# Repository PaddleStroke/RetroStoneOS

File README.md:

# RetroStoneOS

**A fast, minimal retro-gaming OS for the RetroStone2 handheld, and for Raspberry Pi and Orange Pi boards.**

RetroStoneOS boots straight into an EmulationStation-style menu **in about two seconds**, plays games from 40
systems, and switches between the built-in screen and a TV **live, just by plugging HDMI in**. It replaces the old
RetrOrangePi stack (Armbian + RetroPie + RetroArch + EmulationStation) with one small, purpose-built system: mainline
Linux, a single menu/emulation program written in C, and libretro emulator cores. There's no desktop, no X11 and no
layer cake, and every setting lives in one menu.

## Features

**Fast**
- About 2 s from power-on to the logo, and the menu about 0.3 s later. The menu is drawn from a snapshot while game lists load in the background.
- Theme art is prefetched in the background, so a system's first visit in the carousel does not stutter.
- Shutdown in about a second. Powering off during a game saves it; at the next boot the game resumes **Always**, **Ask** or **Never** (your choice).

**Plays well**
- Hardware-scaled video (pixel-perfect 2x on the RetroStone2 LCD) with audio/video sync and dynamic rate control.
- 60 Hz LCD mode, per-game core options, **per-game scaling and CPU profile**, save states with thumbnails, auto-save on exit.
- Each game runs in its own process: a crashing emulator can't take the menu down.
- N64 with GPU rendering and a shader cache, plus an in-game **benchmark** that finds the fastest settings for each game.
- **Rumble** on pads that have motors.

**Laptop-style display switching**
- Plug HDMI in and the picture moves to the TV (720p, or 640x480 for the retro look). Unplug it and it's back on the LCD, even mid-game.
- In docked mode, the controller that starts a game becomes player 1.

**Controls**
- Built-in buttons and the analog stick are handled by the kernel. USB/Bluetooth pads are recognised automatically (SDL GameControllerDB).
- RetroPie hotkeys: **Select+Start** exit, **Select+R/L** save/load state, **Select+Left/Right** state slot, **Select+X** in-game menu, **Select+B** reset.
- **Select+R2** fast-forward, **Select+L2** screenshot, **Select+Y** game switcher (jump between your recent games, each resumed where you left it).
- Remaps per system and per game, including the RetroStone2's optional 6-button Mega Drive layout.

**Finding games**
- **Letter jump** and **search** (in one list or across all games).
- **Play time** per game and a **"Most played"** list, next to favourites and recently played.
- **Hide** or **delete** a game from the menu.

**Getting games on it**
- **SD card in a PC:** the `RETROSTONE` drive, ready right after flashing.
- **USB stick:** plug it in, then *Import games*, *Export games* or *Back up saves*. Copies are incremental, with duplicate handling.
- **WiFi/Ethernet:** a drag-and-drop web page (PIN-protected, with a QR code), or the **Windows share** `\\RETROSTONE`.

**Updates**
- **Signed over-the-air updates** from Settings > System update (WiFi), or offline from a USB drive or the SD card.
- The new system goes to the other A/B slot and is checked before the switch; if it doesn't start, the console goes back to the previous one by itself. Games, saves and settings are never touched. See [docs/updates.md](docs/updates.md).

**Handheld care**
- Battery gauge and warnings, a clean save and shutdown at critical battery, a charge-only mode, and idle dimming.
- **Idle power-off**: after 5 minutes without input (Settings > Power > "Power off after", or Never) the console saves the game and powers off, after a 10 s notice that any button cancels.
- Panel care on the RetroStone2: the LCD keeps receiving a picture whenever it is powered (its "screen off" is backlight off plus a black frame), which protects the panel.
- The SD card is checked after an unexpected power loss, and a hardware watchdog guards against hangs.
- The first boot can't hang on its "Preparing the SD card" screen, and it leaves a step-by-step trace (`rsos/logs/firstboot.txt` on the card) for bug reports.
- WiFi, Bluetooth and Ethernet are **off by default**, so they cost no boot time or battery.

**Looks**
- EmulationStation theme support (drop any ES theme in `themes/`).
- Built-in **rsos-dark** and **rsos-light** themes with console art, plus the **gbz35** themes.
- **22 languages**, chosen at the first boot (English, French, German, Spanish, Italian, Portuguese, Japanese, Chinese, Korean, Russian and more).

## Systems

| Family | Systems |
|---|---|
| RetroStone | 8BCraft's own games, built in: Bomber Mole, Leady Squid, Duck Parade, Blueberry Tumble, Beaver Rush, Pancake Tower and Pogo Mamie (RetroStone VC, [docs/vc-games.md](docs/vc-games.md)) |
| Nintendo | NES, Famicom Disk System, SNES, Nintendo 64, Game Boy, Game Boy Color, Game Boy Advance, Pokémon mini |
| Sega | Master System, Mega Drive/Genesis, Game Gear, SG-1000, 32X, Mega-CD, Pico |
| Sony | PlayStation |
| NEC | PC Engine/TurboGrafx-16, PC Engine CD, SuperGrafx |
| SNK | Neo Geo, Neo Geo CD, Neo Geo Pocket (Color) |
| Arcade | MAME 2003-Plus, FinalBurn Neo |
| Computers | MS-DOS (DOSBox Pure), Commodore 64, ZX Spectrum, Amstrad CPC, MSX |
| Game engines and ports | ScummVM, Doom (Freedoom included), Cave Story, PICO-8 (fake-08) |
| Others | Atari 2600/7800/Lynx, WonderSwan (Color), ColecoVision |

Pre-installed games, so the console is fun out of the box: the **RetroStone** system (Bomber Mole, Leady Squid, Duck Parade, Blueberry Tumble, Beaver Rush, Pancake Tower and Pogo Mamie),
**µCity** (Game Boy Color, GPL-3.0+ / CC BY-SA 4.0) and **Freedoom** (Doom, BSD-3-Clause); see
[docs/homebrew.md](docs/homebrew.md) and [docs/vc-games.md](docs/vc-games.md).
BIOS files go in `RETROSTONE/bios/` (see [docs/cores.md](docs/cores.md)). No commercial games or BIOS files are included.

## Supported hardware

| Board | Defconfig | Status |
|---|---|---|
| **RetroStone2** (8BCraft, Allwinner A20) | `retrostone2` | Primary target, tested |
| RetroStone1 (8BCraft, Allwinner H3) | `retrostone1` | Untested, built by CI; built-in screen (composite) compile-tested only |
| Raspberry Pi 2 (and Pi 3 / Zero 2 W in 32-bit mode) | `rpi2` | Untested, built by CI |
| Raspberry Pi 3 / Zero 2 W (64-bit) | `rpi3_64` | Untested, built by CI |
| Raspberry Pi 4 / 400 / CM4 | `rpi4_64` | Untested, built by CI |
| Raspberry Pi 5 / 500 | `rpi5_64` | Untested, built by CI |
| Orange Pi PC / PC Plus (H3) | `orangepi_h3_pc` | Untested, built by CI |
| Orange Pi One / Lite (H3) | `orangepi_h3_one` | Untested, built by CI |
| Orange Pi 5 (RK3588S) | `orangepi5` | Untested, built by CI |

The single-board computer images are built automatically by CI, but nobody has booted them on the board yet: they
are HDMI boxes for USB/Bluetooth pads. Please open an issue with your results! Details in [docs/boards.md](docs/boards.md);
adding a board takes one folder and a `board.ini` profile ([docs/porting.md](docs/porting.md)).

## Install

1. Download the image for your board from [**Releases**](https://github.com/PaddleStroke/RetroStoneOS/releases).
2. Flash it to a microSD card of 2 GB or more (4 GB for the Orange Pi 5) with [balenaEtcher](https://etcher.balena.io/) or [Rufus](https://rufus.ie/).
3. Copy your games into `RETROSTONE/roms/<system>/`, from the PC (the drive appears right after flashing), from a USB stick, or over WiFi later.
4. Boot. The first start prepares the SD card and asks for your language, then the menu appears.

Later versions install from the console itself (Settings > System update); no reflashing needed.

## Build from source

RetroStoneOS is a [Buildroot](https://buildroot.org/) external tree. On Linux (or WSL2):

```sh
wget https://buildroot.org/downloads/buildroot-2026.02.3.tar.xz && tar xf buildroot-2026.02.3.tar.xz
cd buildroot-2026.02.3
make BR2_EXTERNAL=/path/to/RetroStoneOS/buildroot-external retrostone2_defconfig   # or rpi4_64_defconfig, ...
make
# -> output/images/sdcard.img
```

The RetroStone games build from a [RetroStone VC](https://github.com/PaddleStroke/RetroStoneVC) checkout next to
this one (`../RetroStoneVC`; or set `BR2_PACKAGE_RSOS_VC_GAMES=n`, docs/vc-games.md). The menu
program also builds and tests on a PC: `cd frontend && make check`. Details: [docs/build.md](docs/build.md).

## Documentation

| | |
|---|---|
| [build.md](docs/build.md) | Building, the SD layout, A/B slots, boot time, the release build |
| [boards.md](docs/boards.md) · [porting.md](docs/porting.md) | Supported boards; adding a board |
| [cores.md](docs/cores.md) | Emulators, BIOS files, ROM folders, performance |
| [ui-design.md](docs/ui-design.md) | The menu, themes, settings |
| [host-design.md](docs/host-design.md) | The libretro game host (hotkeys, fast-forward, screenshots, game switcher) |
| [input-design.md](docs/input-design.md) | Controls, remaps, rumble |
| [display-design.md](docs/display-design.md) | LCD/HDMI switching and scaling |
| [rom-transfer.md](docs/rom-transfer.md) | USB, web page and Windows share |
| [updates.md](docs/updates.md) | Signed system updates (`.rsu` packages, keys) |
| [power.md](docs/power.md) | Battery, charging, shutdown |
| [translating.md](docs/translating.md) | Adding or fixing a translation |
| [homebrew.md](docs/homebrew.md) | The bundled games and their licences |
| [vc-games.md](docs/vc-games.md) | The RetroStone system: 8BCraft's own games (RetroStone VC) |
| [ci.md](docs/ci.md) | CI, releases and the repository secrets |
| [hardware-pinmap.md](docs/hardware-pinmap.md) · [kernel-patches.md](docs/kernel-patches.md) | RetroStone2 hardware and kernel patches |
| [bringup.md](docs/bringup.md) | Hardware test script ([bring-up logs](docs/bringup-logs/)) |
| [hardware/](hardware/) | RetroStone2 schematic, PCB and Gerber files; RetroStone1 schematic and PCB |
| [CONVENTIONS.md](docs/CONVENTIONS.md) · [requirements.md](docs/requirements.md) · [review/](docs/review/) | Project conventions, requirements and reviews |

## License

The RetroStoneOS code is under the [MIT License](LICENSE). Bundled third-party components keep their own licences (the
Linux kernel and U-Boot under GPL-2.0, the emulator cores under various licences including some non-commercial ones,
the Carbon/gbz35 theme art under CC BY-NC-SA, and the RetroStone games under MIT (code) and CC BY-NC-SA 4.0 (art,
music, levels)). See [LICENSE](LICENSE) for the details, and each release's
`legal-info` archive for the full sources and licence texts. The hardware files in `hardware/` (RetroStone2 and
RetroStone1) are open hardware under the [CERN-OHL-P-2.0](hardware/LICENSE.txt) (see [hardware/README.md](hardware/README.md)).

**The images are free, for non-commercial use.** RetroStoneOS is a free download and is not sold with any hardware.
Its images include non-commercial emulator cores (snes9x2005/2010, PicoDrive, MAME 2003-Plus, FBNeo) and CC BY-NC-SA
theme art, so an image must not be sold, and must not be preloaded on hardware that is sold (a console, an SD card
or a kit). Sharing the images for free is fine.

## Credits

- The RetroStone2 handheld: **Pierre-Louis Boyer / 8BCraft**.
- The [libretro](https://www.libretro.com/) core authors, [Buildroot](https://buildroot.org/), the
  [linux-sunxi](https://linux-sunxi.org/) community and the mainline kernel developers.
- Olimex, for the original A20 HDMI audio driver work.
- Themes: rxbrad (gbz35) and Rookervik (Carbon, RetroPie).
- Antonio Niño Díaz for µCity, and the Freedoom project (see [docs/homebrew.md](docs/homebrew.md)).

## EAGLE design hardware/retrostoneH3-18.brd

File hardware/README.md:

# RetroStone hardware files

Design files of the RetroStone2 main board (Allwinner A20) and of the RetroStone1 (Allwinner H3), by Pierre-Louis
Boyer / 8BCraft. The RetroStone2 files are the source of
truth for the pin map in [docs/hardware-pinmap.md](../docs/hardware-pinmap.md) and for the device tree
(`buildroot-external/board/retrostone2/dts/`). The folder also holds the RetroStone1 (Allwinner H3) schematic and
layout, the source of `buildroot-external/board/retrostone1/dts/`.

| File | Content |
|---|---|
| `retrostoneA20-1.15.sch` | schematic, board revision 1.15 (Eagle 7.6, XML) |
| `retrostoneA20-1.15.brd` | PCB layout, revision 1.15 (Eagle 7.6, XML) |
| `retrostoneA20-1.15.pdf` | the schematic as a PDF |
| `retrostone2_v1.15.zip` | Gerber and drill files, revision 1.15 |
| `retrostoneA20-1.08.xls` | bill of materials, revision 1.08 (older board) |
| `retrostoneH3-18.sch` | **RetroStone1** (Allwinner H3) schematic, revision 1.18 (Eagle 7.6, XML); source of `buildroot-external/board/retrostone1/dts/` (docs/boards.md, "RetroStone1") |
| `retrostoneH3-18.brd` | RetroStone1 PCB layout, revision 1.18 (Eagle 7.6, XML) |
| `RSN1-1.18.pdf` | the RetroStone1 schematic as a PDF (vector drawing, no text layer) |
| `tools/eagle_nets.py` | lists the parts and nets of a `.sch`: `python3 tools/eagle_nets.py <sch> parts\|part <name>\|net <name>` |
| `tools/eagle_parts_pos.py` | prints the board position of parts from a `.brd`: `python3 tools/eagle_parts_pos.py <brd> K1 K2 ...` |

## Known design notes (for future revisions)

- **RetroStone1: MCP3208 CH2 wired straight to VBAT.** The battery voltage goes to the ADC input without a divider:
  a charged cell (4.2 V) is above the MCP3208's absolute maximum input (VDD + 0.6 V at 3.3 V), and while the 3.3 V
  rail is off the input's protection diode back-feeds that rail from the battery. The owner does not plan to
  produce this board again; a new revision should use a divider (e.g. 2 x 100k, with a small capacitor) or a
  dedicated gauge.
- **RetroStone2: the panel VCC is the always-on 3.3 V rail**, and that rail (buck U17) is enabled by the AXP209
  EXTEN output together with the 5 V boost and the speaker amplifier: a load switch on the panel VCC driven by a
  free GPIO is worth adding (docs/hardware-pinmap.md, "Panel power" and "Power").

## Licence

The design files in this folder (not `tools/`) are open hardware, © 2026 Pierre-Louis Boyer / 8BCraft, licensed
under the **CERN Open Hardware Licence Version 2 – Permissive** (SPDX: `CERN-OHL-P-2.0`, full text in
[LICENSE.txt](LICENSE.txt)). You may study, modify, make and sell boards from them; keep the copyright and licence
notices. The scripts in `tools/` are under the MIT licence of the RetroStoneOS software ([LICENSE](../LICENSE)).
"RetroStone" and "8BCraft" are names of 8BCraft: a derived board should not be sold under them.

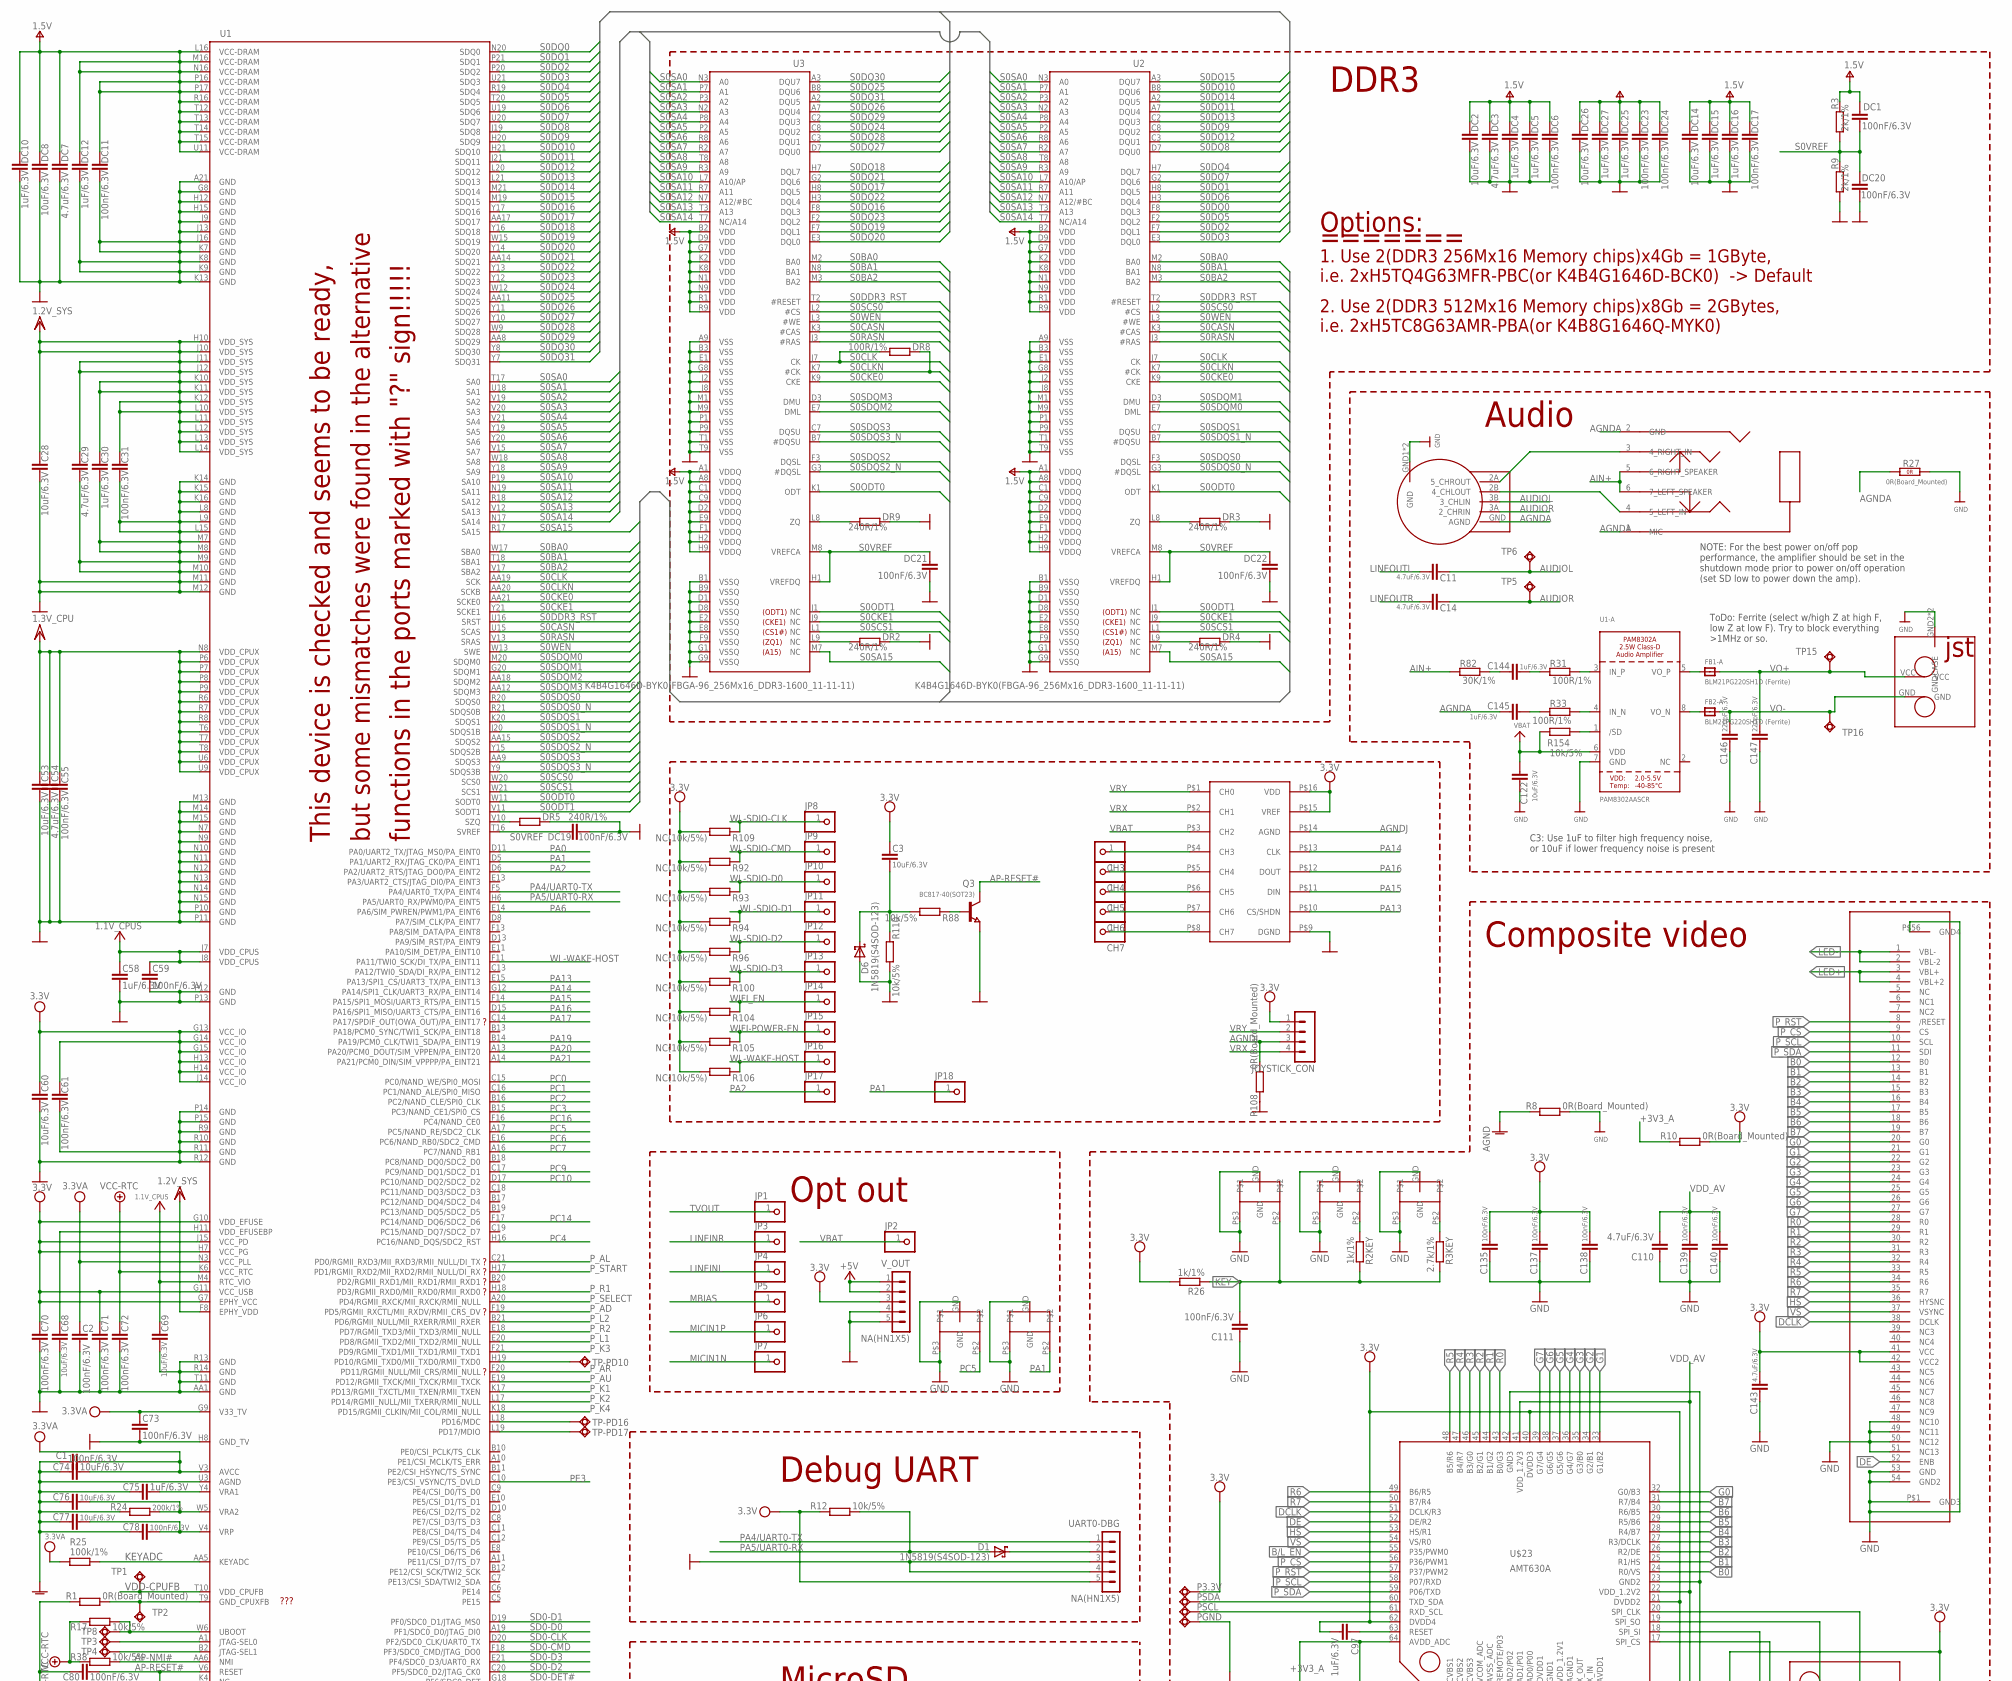
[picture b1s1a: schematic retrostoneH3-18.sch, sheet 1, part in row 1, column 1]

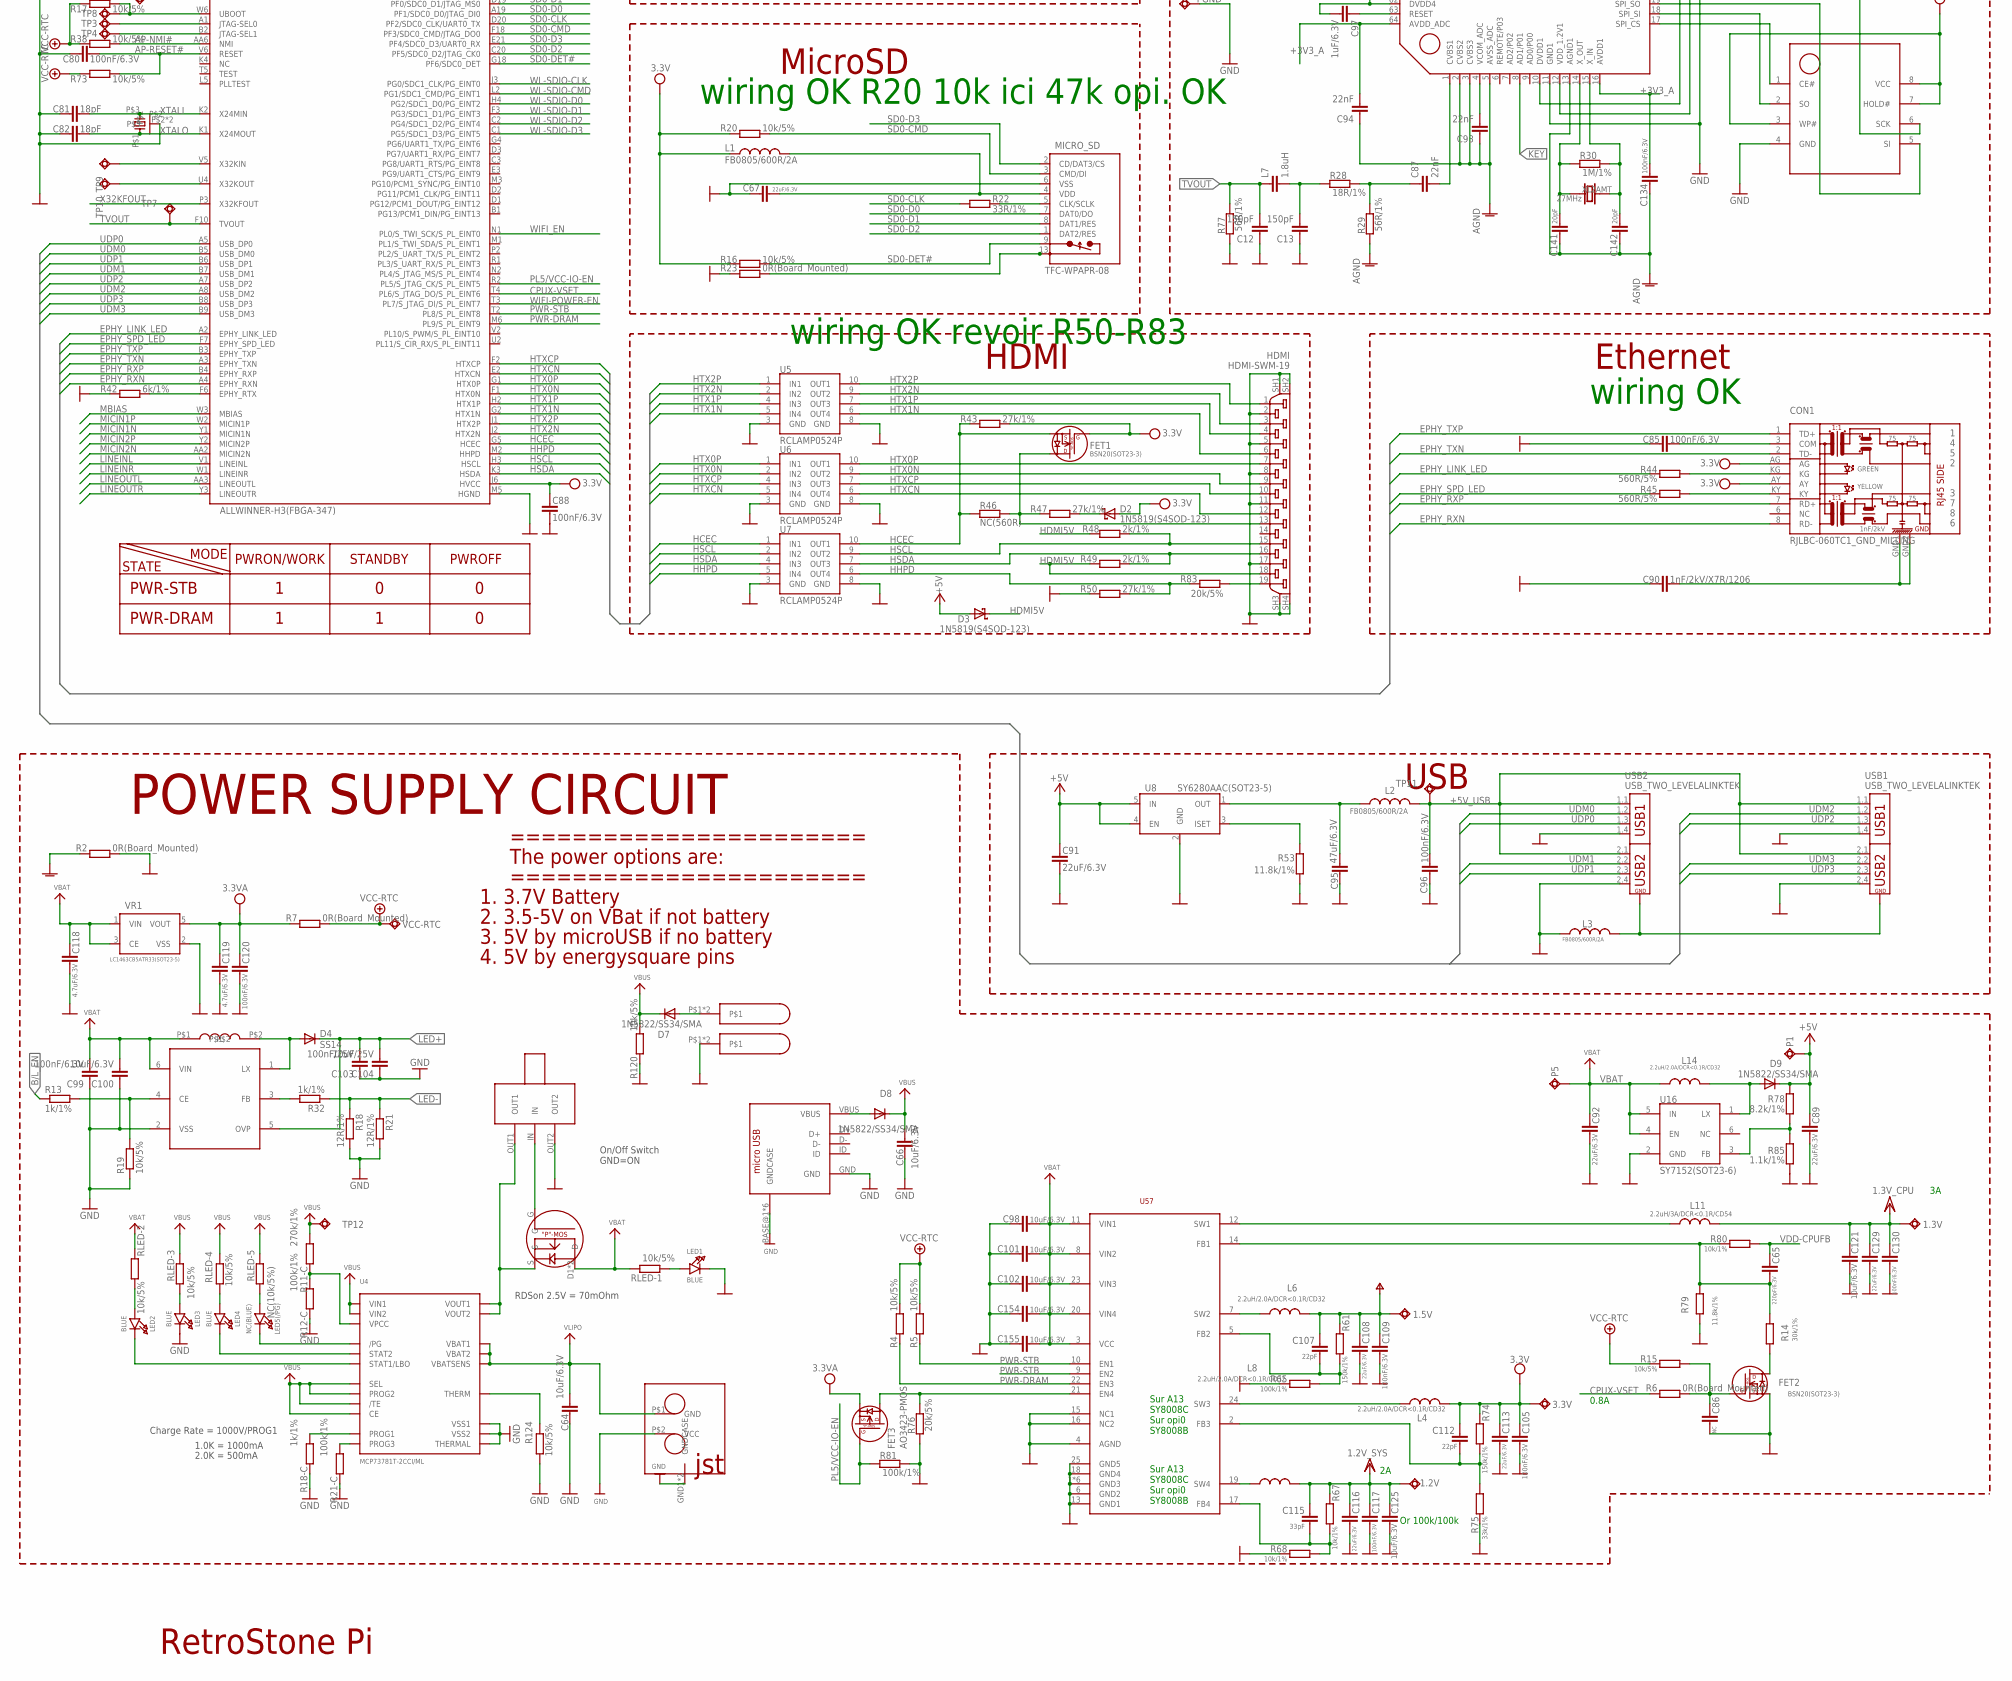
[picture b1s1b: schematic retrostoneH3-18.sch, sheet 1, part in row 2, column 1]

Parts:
1.2V, 1.3V, 1.5V, 3.3V: TESTPADTESTPAD_40-ROUND; TESTPAD_40-ROUND
C1, C2, C31, C55, C59, C61, C70, C71, C72, C73, C78, C80, C85, C88, C96, C99, C105, C109, C111, C117, C120, C130, C134, C135, C137, C138, C139, C140: 100nF/6.3V; C0402_TI
C3, C28, C53, C60, C64, C66, C68, C69, C74, C76, C77, C98, C100, C101, C102, C121, C122, C125, C154, C155: 10uF/6.3V; C0603_DWS
C11, C14, C29, C54, C110, C118, C119, C143: 4.7uF/6.3V; C0603_DWS
C12, C13: 150pF; C0402_TI
C30, C58, C75, C97, C144, C145: 1uF/6.3V; C0402_TI
C65, C146, C147: 220pF/6.3V; C0402_TI
C67, C89, C91, C92, C108, C113, C116, C129: 22uF/6.3V; C0603_DWS
C81, C82: 18pF; C0402_TI
C86: NC; C0402_TI
C87, C93, C94: 22nF; C0402_TI
C90: 1nF/2kV/X7R/1206; C1206_5MILS_WS_ISO
C95: 47uF/6.3V; C0805_5MIL_DWS
C103: 100nF/25V; C0805_5MIL
C104: 10uF/25V; C0805_5MIL
C107, C112: 22pF; C0402_TI
C115: 33pF; C0402_TI
C141, C142: 20pF; C0402_TI
CH3, CH4, CH5, CH6, CH7: PINHD-1X1; 1X01
CON1: RJLBC-060TC1_GND_MILLING; RJLBC-060TC1_MILLING
D1, D2, D3, D6: 1N5819(S4SOD-123); SOD-123
D4: SS14; DO214AC
D7, D8, D9: 1N5822/SS34/SMA; MELF-MLL41
DC1, DC6, DC11, DC17, DC19, DC20, DC21, DC22, DC23, DC24: 100nF/6.3V; C0402_TI
DC2, DC8, DC14, DC26: 10uF/6.3V; C0603_DWS
DC3, DC7: 4.7uF/6.3V; C0603_DWS
DC4, DC5, DC10, DC12, DC15, DC16, DC25, DC27: 1uF/6.3V; C0402_TI
DR2, DR3, DR4, DR5, DR9: 240R/1%; R0402_TI
DR8: 100R/1%; R0402_TI
ENERGYSQUARE_GND: CONTACTPIN_ENERGYSQUARE1MM; CONTACTPIN_ENERGYSQUARE_OD_1MM
ENERGYSQUARE_VBUS: CONTACTPIN_ENERGYSQUARE1MM; CONTACTPIN_ENERGYSQUARE_OD_1MM
FB1-A, FB2-A: BLM21PG220SH1D (Ferrite); _0805
FET1, FET2: BSN20(SOT23-3); SOT23
FET3: AO3423-PMOS; SOT23
FPC54P: FPC_HAYATO
HDMI: HDMI-SWM-19
JOYSTICK_CON: MA04-1
JP1, JP2, JP3, JP4, JP5, JP6, JP7, JP8, JP9, JP10, JP11, JP12, JP13, JP14, JP15, JP16, JP17, JP18: PINHD-1X1; 1X01
L1, L2, L3: FB0805/600R/2A; L0805_5MIL_DWS
L4, L6, L8, L14: 2.2uH/2.0A/DCR<0.1R/CD32; CD32
L5: 22uH/CD32; CD32_INDUCTOR
L7: 1.8uH; C0402_TI
L11: 2.2uH/3A/DCR<0.1R/CD54; CD52(53)
LED1, LED2, LED3, LED4: BLUE; CHIPLED_0805_NOOUTLINE
LED5(/PG): NC(BLUE); CHIPLED_0805_NOOUTLINE
MICRO_SD: TFC-WPAPR-08
P1, P3.3V, P5: TESTPADTESTPAD_40-ROUND; TESTPAD_40-ROUND
PGND: TESTPADTESTPAD_40-ROUND; TESTPAD_40-ROUND
PSCL: TESTPADTESTPAD_40-ROUND; TESTPAD_40-ROUND
PSDA: TESTPADTESTPAD_40-ROUND; TESTPAD_40-ROUND
Q1: 24MHz 9pF TSX-3225; TSX-3225
Q3: BC817-40(SOT23); SOT23
R1, R2, R6, R7, R8, R10, R23, R108: 0R(Board_Mounted); R0402_TI_0R
R2KEY, R13, R18-C, R26, R32: 1k/1%; R0402_TI
R3, R9, R48, R49: 2k/1%; R0402_TI
R3KEY: 2.7k/1%; R0402_TI
R4, R5, R12, R15, R16, R17, R19, R20, R38, R73, R88, R110, R120, R124, R154: 10k/5%; R0402_TI
R11-C: 270k/1%; R0402_TI
R12-C, R21-C, R25, R65, R81: 100k/1%; R0402_TI
R14: 30k/1%; R0402_TI
R18, R21: 12R/1%; R0603_5MIL_DWS
R22: 33R/1%; R0402_TI
R24: 200k/1%; R0402_TI
R27: 0R(Board_Mounted); 0603_0R
R28: 18R/1%; R0402_TI
R29, R77: 56R/1%; R0402_TI
R30: 1M/1%; R0402_TI
R31, R33: 100R/1%; R0402_TI
R42: 6k/1%; R0402_TI
R43, R47, R50: 27k/1%; R0603_5MIL_DWS
R44, R45: 560R/5%; R0603_5MIL_DWS
R46: NC(560R); R0603_5MIL_DWS
R53, R79: 11.8k/1%; R0402_TI
R61, R74: 150k/1%; R0402_TI
R67, R68, R80: 10k/1%; R0402_TI
R75: 33k/1%; R0402_TI
R76, R83: 20k/5%; R0402_TI
R78: 8.2k/1%; R0402_TI
R82: 30K/1%; R0402_TI
R85: 1.1k/1%; R0402_TI
R92, R93, R94, R96, R100, R104, R105, R106, R109: NC(10k/5%); R0402_TI
RLED-1, RLED-2, RLED-3, RLED-4: 10k/5%; R0402_TI
RLED-5: NC(10k/5%); R0402_TI
TP1, TP2, TP3, TP4, TP5, TP6, TP7, TP8, TP9, TP10, TP11, TP12, TP15, TP16: TESTPADTESTPAD_40-ROUND; TESTPAD_40-ROUND
TP-PD10, TP-PD16, TP-PD17: TESTPADTESTPAD_40-ROUND; TESTPAD_40-ROUND
U1: ALLWINNER-H3(FBGA-347); FBGA-347
U1-A: PAM8302AASCR; MSOP8_0.65MM
U2, U3: K4B4G1646D-BYK0(FBGA-96_256Mx16_DDR3-1600_11-11-1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; FBGA96(HYNIX_SAMSUNG_512MX16_DDR3)
U4: MCP73781T-2CCI/ML; QFN20_4MM
U5, U6, U7: RCLAMP0524P; SLP2510P8
U8: SY6280AAC(SOT23-5); SOT23-5
U16: SY7152(SOT23-6); SOT23-6
U57: AXP8036; QFN4X4
U$6: SS-12F21(1P2T)
U$8: JST_PH_VERT_2P
U$11: CSD22205L
U$14: KA2707; SOT23-6
U$15, U$36, U$37, U$38: TACT_SWITCH_HORIZONTAL
U$17: MICROUSB_HAYATO
U$18: PM25LV512; SOIC8
U$23: AMT630A; LQFP-ST-64-2
U$24: PJ342_5PIN; PJ342_6P
U$27: WHEEL_POT
U$29: JST2_HAYATO
U$33: NC/(TACT_SWITCH_HORIZONTAL); TACT_SWITCH_HORIZONTAL
U$35: MCP3208
UART0-DBG: NA(HN1X5); HN1X5
USB1, USB2: USB_TWO_LEVELALINKTEK; USB_TWO_LEVEL_ALINKTEK
VCC-RTC: TESTPADTESTPAD_40-ROUND; TESTPAD_40-ROUND
VR1: LC1463CB5ATR33(SOT23-5); SOT-23-5
V_OUT: NA(HN1X5); HN1X5
XL2AMT: 27MHz; HC49UP

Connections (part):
+3V3_A: C94.2, C134.2, R10.2, U$23.16 (AVDD1), U$23.64 (AVDD_ADC)
+5V: C89.1, C91.1, D3.A, D9.1 (C), P1.1, R78.2, U8.4 (EN), U8.5 (IN), V_OUT.1, V_OUT.2
+5V_USB: C96.1, L2.1, TP11.1, USB1.1.1, USB1.2.1, USB2.1.1, USB2.2.1
+7V: C72.2, R4.1, R5.1, R7.1, R15.1, R17.1, R38.2, R73.1, U1.K6 (VCC_RTC), VCC-RTC.1
AD0/P00: U$23.9 (AD0/P00)
AGND: C93.1, C94.1, C134.1, C141.1, C142.1, R8.2, R29.1, U$23.2 (CVBS2), U$23.3 (CVBS3), U$23.5 (AVSS_ADC), U$23.13 (AGND1)
AGNDA: C145.1, R27.2 (1.2), U$24.1 (MIC), U$24.2 (GND), U$27.GND (AGND)
AGNDJ: JOYSTICK_CON.3, R108.1, U$35.P$14 (AGND)
AIN+: R82.1, U$24.5 (6_RIGHT_SPEAKER), U$24.6 (7_LEFT_SPEAKER)
AP-NMI#: R38.1, U1.AA6 (NMI)
AP-RESET#: C80.2, Q3.3 (C), R73.2, U1.V6 (RESET)
AUDIOL: C11.1, TP6.1, U$27.3B (3_CHLIN)
AUDIOR: C14.1, TP5.1, U$27.3A (2_CHRIN)
B0: FPC54P.12 (B0), U$23.24 (R0/VS)
B1: FPC54P.13 (B1), U$23.25 (R1/HS)
B2: FPC54P.14 (B2), U$23.26 (R2/DE)
B3: FPC54P.15 (B3), U$23.27 (R3/DCLK)
B4: FPC54P.16 (B4), U$23.28 (R4/B7)
B5: FPC54P.17 (B5), U$23.29 (R5/B6)
B6: FPC54P.18 (B6), U$23.30 (R6/B5)
B7: FPC54P.19 (B7), U$23.31 (R7/B4)
B/L_EN: R13.1, U$23.55 (P35/PWM0)
CH3: CH3.1, U$35.P$4 (CH3)
CPUX-VSET: R6.2, U1.T4 (PL6/S_JTAG_DO/S_PL_EINT6)
DCLK: FPC54P.38 (DCLK), U$23.51 (DCLK/R3)
DE: FPC54P.52 (ENB), U$23.52 (DE/R2)
ENABLE: U$6.IN, U$11.G
EPHY_LINK_LED: R44.2, U1.A2 (EPHY_LINK_LED)
EPHY_RXN: CON1.8 (RD-), U1.A4 (EPHY_RXN)
EPHY_RXP: CON1.7 (RD+), U1.B4 (EPHY_RXP)
EPHY_SPD_LED: R45.2, U1.F7 (EPHY_SPD_LED)
EPHY_TXN: CON1.2 (TD-), U1.A3 (EPHY_TXN)
EPHY_TXP: CON1.1 (TD+), U1.B3 (EPHY_TXP)
G0: FPC54P.20 (G0), U$23.32 (G0/B3)
G1: FPC54P.21 (G1), U$23.33 (G1/B2)
G2: FPC54P.22 (G2), U$23.34 (G2/B1)
G3: FPC54P.23 (G3), U$23.35 (G3/B0)
G4: FPC54P.24 (G4), U$23.36 (G4/G7)
G5: FPC54P.25 (G5), U$23.37 (G5/G6)
G6: FPC54P.26 (G6), U$23.38 (G6/G5)
G7: FPC54P.27 (G7), U$23.39 (G7/G4)
GND: C2.1, C12.1, C13.1, C28.2, C29.1, C30.1, C31.1, C53.2, C54.2, C55.1, C58.2, C59.1, C60.2, C61.1, C64.1, C66.1, C67.1, C68.2, C69.2, C70.1, C71.1, C72.1, C73.1, C80.1, C81.1, C82.1, C85.1, C86.2, C88.1, C89.2, C90.1, C91.2, C92.1, C95.2, C96.2, C98.1, C99.1, C100.1, C101.1, C102.1, C103.1, C104.1, C105.2, C108.2, C109.2, C110.1, C111.1, C113.2, C116.2, C117.2, C118.2, C119.2, C120.2, C121.1, C122.1, C125.1, C129.2, C130.2, C135.1, C137.1, C138.1, C139.1, C140.1, C143.1, C146.1, C147.1, C154.1, C155.1, D6.A, DC2.2, DC3.2, DC4.1, DC5.1, DC6.1, DC7.2, DC8.2, DC10.1, DC11.1, DC12.1, DC14.2, DC15.1, DC16.1, DC17.1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; also elsewhere on the board
GNDA: C1.2, C74.1, C75.1, C76.1, C77.1, C78.1, R2.2, R24.2, U1.U3 (AGND)
HCEC: FET1.2 (S), R43.1, R46.2, U1.G5 (HCEC), U7.1 (IN1), U7.10 (OUT1)
HDMI5V: D3.C, HDMI.18, R48.2, R49.2
HHPD: R50.1, R83.1, U1.M2 (HHPD), U7.5 (IN4), U7.6 (OUT4)
HS: FPC54P.36 (HYSNC), U$23.53 (HS/R1)
HSCL: HDMI.15, R48.1, U1.H3 (HSCL), U7.2 (IN2), U7.9 (OUT2)
HSDA: HDMI.16, R49.1, U1.K3 (HSDA), U7.4 (IN3), U7.7 (OUT3)
HTX0N: HDMI.9, U1.F1 (HTX0N), U6.2 (IN2), U6.9 (OUT2)
HTX0P: HDMI.7, U1.G1 (HTX0P), U6.1 (IN1), U6.10 (OUT1)
HTX1N: HDMI.6, U1.G2 (HTX1N), U5.5 (IN4), U5.6 (OUT4)
HTX1P: HDMI.4, U1.H2 (HTX1P), U5.4 (IN3), U5.7 (OUT3)
HTX2N: HDMI.3, U1.J2 (HTX2N), U5.2 (IN2), U5.9 (OUT2)
HTX2P: HDMI.1, U1.J1 (HTX2P), U5.1 (IN1), U5.10 (OUT1)
HTXCN: HDMI.12, U1.E2 (HTXCN), U6.5 (IN4), U6.6 (OUT4)
HTXCP: HDMI.10, U1.F2 (HTXCP), U6.4 (IN3), U6.7 (OUT3)
KEY: C111.2, R2KEY.2, R3KEY.2, R26.1, U$23.8 (AD1/P01), U$36.P$2
KEYADC: R25.1, U1.AA5 (KEYADC)
LED+: C103.2, C104.2, D4.C, FPC54P.3 (VBL+), FPC54P.4 (VBL+2), U$14.5 (OVP)
LED-: FPC54P.1 (VBL-), FPC54P.2 (VBL-2), R18.1, R21.1, R32.1
LINEINL: JP4.1, U1.V1 (LINEINL)
LINEINR: JP3.1, U1.W1 (LINEINR)
LINEOUTL: C11.2, U1.AA3 (LINEOUTL)
LINEOUTR: C14.2, U1.Y3 (LINEOUTR)
LR: U$24.3 (4_RIGHT_IN), U$27.2A (5_CHROUT)
MBIAS: JP5.1, U1.W3 (MBIAS)
MICIN1N: JP7.1, U1.Y1 (MICIN1N)
MICIN1P: JP6.1, U1.W2 (MICIN1P)
MICIN2N: U1.AA2 (MICIN2N)
MICIN2P: U1.Y2 (MICIN2P)
unnamed: MICRO_SD.5 (CLK/SCLK), R22.1
unnamed: DR5.2, U1.V10 (SZQ)
unnamed: DR9.2, U3.L8 (ZQ)
unnamed: D2.C, R47.1
unnamed: DR3.2, U2.L8 (ZQ)
unnamed: DR2.2, U3.L9 (NC)
unnamed: D1.C, UART0-DBG.2
unnamed: R1.1, TP2.1, U1.T9 (GND_CPUXFB)
unnamed: L8.1, U57.19 (SW4)
unnamed: TP4.1, U1.B2 (JTAG-SEL1)
unnamed: DR4.2, U2.L9 (NC)
unnamed: FET2.3 (D), R14.2
unnamed: HDMI.19, R83.2
unnamed: C75.2, U1.Y4 (VRA1)
unnamed: C87.1, R28.2, R29.2
unnamed: C87.2, U$23.1 (CVBS1)
unnamed: C93.2, U$23.4 (VCOM_ADC)
unnamed: C97.1, U$23.63 (RESET)
unnamed: U4.P$1 (VOUT1), U4.P$20 (VOUT2), U$6.OUT1, U$11.S
unnamed: R53.2, U8.3 (ISET)
unnamed: R2KEY.1, U$37.P$2
unnamed: R13.2, R19.2, U$14.4 (CE)
unnamed: D4.A, L5.P$2, U$14.1 (LX)
unnamed: C86.1, FET2.1 (G), R6.1, R15.2
unnamed: R32.2, U$14.3 (FB)
unnamed: L6.1, U57.7 (SW2)
unnamed: C95.1, L2.2, U8.1 (OUT)
unnamed: FET1.3 (D), HDMI.13, R46.1, R47.2
unnamed: R17.2, TP8.1, U1.W6 (UBOOT)
unnamed: LED3.A, RLED-3.1
unnamed: C90.2, CON1.GND1, CON1.GND2
unnamed: LED2.A, RLED-2.1
unnamed: L11.1, U57.12 (SW1)
unnamed: TP3.1, U1.A1 (JTAG-SEL0)
unnamed: LED1.A, RLED-1.1
unnamed: Q3.1 (B), R88.2
unnamed: LED4.A, RLED-4.2
unnamed: L4.1, U57.24 (SW3)
unnamed: TP10.1, U1.U4 (X32KOUT)
unnamed: TP9.1, U1.V5 (X32KIN)
unnamed: C107.2, R61.2, R65.1, U57.5 (FB2)
unnamed: TP-PD16.1, U1.L18 (PD16/MDC)
unnamed: C112.2, R74.2, R75.1, U57.2 (FB3)
unnamed: C3.2, D6.C, R88.1, R110.2
unnamed: FET3.3 (D), R76.2, U57.21 (EN4)
unnamed: TP-PD17.1, U1.L19 (PD17/MDIO)
unnamed: C144.1, R82.2
unnamed: C115.2, R67.2, R68.1, U57.17 (FB4)
unnamed: CH4.1, U$35.P$5 (CH4)
unnamed: R3KEY.1, U$38.P$2
unnamed: C65.2, R14.1, R79.1, R80.1, U57.14 (FB1)
unnamed: CON1.KG, R44.1
unnamed: TP-PD10.1, U1.H19 (PD10/RGMII_TXD0/MII_TXD0/RMII_TXD0)
unnamed: R42.1, U1.F6 (EPHY_RTX)
unnamed: C85.2, CON1.3 (COM)
unnamed: CON1.KY, R45.1
unnamed: MICRO_SD.10 (PACK1), MICRO_SD.11 (PACK2), MICRO_SD.12 (PACK3), MICRO_SD.13 (PACK4), R23.1
unnamed: R11-C.2, R12-C.1, U4.P$2 (VPCC)
unnamed: LED4.C, U4.P$7 (STAT2)
unnamed: LED2.C, U4.P$8 (STAT1/LBO)
unnamed: R18-C.1, U4.P$13 (PROG1)
unnamed: R124.1, U4.P$5 (THERM)
unnamed: R154.2, U1-A.1 (/SD)
unnamed: LED5(/PG).A, RLED-5.1
unnamed: R21-C.1, U4.P$12 (PROG3)
unnamed: LED5(/PG).C, U4.P$6 (/PG)
unnamed: D7.2 (A), ENERGYSQUARE_VBUS.P$1, ENERGYSQUARE_VBUS.P$2
unnamed: C13.2, L7.2, R28.1
unnamed: R33.2, U1-A.4 (IN_N)
unnamed: R31.2, U1-A.3 (IN_P)
unnamed: C145.2, R33.1
unnamed: FB2-A.1, U1-A.8 (VO_N)
unnamed: FB1-A.1, U1-A.5 (VO_P)
unnamed: C144.2, R31.1
unnamed: U$24.4 (5_LEFT_IN), U$27.2B (4_CHLOUT)
unnamed: D8.2 (A), U$17.VBUS
unnamed: CH5.1, U$35.P$6 (CH5)
unnamed: CH6.1, U$35.P$7 (CH6)
unnamed: CH7.1, U$35.P$8 (CH7)
unnamed: C77.2, C78.2, U1.V4 (VRP)
unnamed: D9.2 (A), L14.2, U16.1 (LX)
unnamed: R78.1, R85.1, U16.3 (FB)
unnamed: C76.2, R24.1, U1.W5 (VRA2)
unnamed: L3.2, USB1.GND1, USB1.GND2 (GND1), USB1.GND3 (GND1), USB1.GND4 (GND1), USB2.GND1, USB2.GND2 (GND1), USB2.GND3 (GND1), USB2.GND4 (GND1)
PA0: U1.D11 (PA0/UART2_TX/JTAG_MS0/PA_EINT0); also elsewhere on the board
PA1: JP18.1, U1.D5 (PA1/UART2_RX/JTAG_CK0/PA_EINT1), U$15.P$2; also elsewhere on the board
PA2: JP17.1, U1.D6 (PA2/UART2_RTS/JTAG_DO0/PA_EINT2); also elsewhere on the board
PA4/UART0-TX: U1.F5 (PA4/UART0_TX/PA_EINT4), UART0-DBG.1
PA5/UART0-RX: D1.A, R12.1, U1.H6 (PA5/UART0_RX/PWM0/PA_EINT5)
PA6: U1.E14 (PA6/SIM_PWREN/PWM1/PA_EINT6); also elsewhere on the board
PA13: U1.E15 (PA13/SPI1_CS/UART3_TX/PA_EINT13), U$35.P$10 (CS/SHDN); also elsewhere on the board
PA14: U1.G12 (PA14/SPI1_CLK/UART3_RX/PA_EINT14), U$35.P$13 (CLK); also elsewhere on the board
PA15: U1.F14 (PA15/SPI1_MOSI/UART3_RTS/PA_EINT15), U$35.P$11 (DIN); also elsewhere on the board
PA16: U1.D15 (PA16/SPI1_MISO/UART3_CTS/PA_EINT16), U$35.P$12 (DOUT); also elsewhere on the board
PA17: U1.C14 (PA17/SPDIF_OUT(OWA_OUT)/PA_EINT17); also elsewhere on the board
PA19: U1.B14 (PA19/PCM0_CLK/TWI1_SDA/PA_EINT19); also elsewhere on the board
PA20: U1.A13 (PA20/PCM0_DOUT/SIM_VPPEN/PA_EINT20); also elsewhere on the board
PA21: U1.A14 (PA21/PCM0_DIN/SIM_VPPPP/PA_EINT21); also elsewhere on the board
PC0: U1.C15 (PC0/NAND_WE/SPI0_MOSI); also elsewhere on the board
PC1: U1.C16 (PC1/NAND_ALE/SPI0_MISO); also elsewhere on the board
PC2: U1.B16 (PC2/NAND_CLE/SPI0_CLK); also elsewhere on the board
PC3: U1.B15 (PC3/NAND_CE1/SPI0_CS); also elsewhere on the board
PC4: U1.H16 (PC16/NAND_DQS/SDC2_RST); also elsewhere on the board
PC5: U1.A17 (PC5/NAND_RE/SDC2_CLK), U$33.P$2; also elsewhere on the board
PC6: U1.E16 (PC6/NAND_RB0/SDC2_CMD); also elsewhere on the board
PC7: U1.A16 (PC7/NAND_RB1); also elsewhere on the board
PC9: U1.C17 (PC9/NAND_DQ1/SDC2_D1); also elsewhere on the board
PC10: U1.D17 (PC10/NAND_DQ2/SDC2_D2); also elsewhere on the board
PC14: U1.F17 (PC14/NAND_DQ6/SDC2_D6); also elsewhere on the board
PC16: U1.F16 (PC4/NAND_CE0); also elsewhere on the board
PE3: U1.C10 (PE3/CSI_VSYNC/TS_DVLD); also elsewhere on the board
PL5/VCC-IO-EN: FET3.1 (G), R81.1, U1.R2 (PL5/S_JTAG_CK/S_PL_EINT5)
PWR-DRAM: R4.2, U1.M6 (PL9/S_PL_EINT9), U57.22 (EN3)
PWR-STB: R5.2, U1.T2 (PL8/S_PL_EINT8), U57.9 (EN2), U57.10 (EN1)
P_AD: U1.F19 (PD5/RGMII_RXCTL/MII_RXDV/RMII_CRS_DV); also elsewhere on the board
P_AL: U1.C21 (PD0/RGMII_RXD3/MII_RXD3/RMII_NULL/DI_TX); also elsewhere on the board
P_AR: U1.F20 (PD11/RGMII_NULL/MII_CRS/RMII_NULL); also elsewhere on the board
P_AU: U1.E19 (PD12/RGMII_TXCK/MII_TXCK/RMII_TXCK); also elsewhere on the board
P_CS: FPC54P.9 (CS), U$23.56 (P36/PWM1)
P_K1: U1.K17 (PD13/RGMII_TXCTL/MII_TXEN/RMII_TXEN); also elsewhere on the board
P_K2: U1.L17 (PD14/RGMII_NULL/MII_TXERR/RMII_NULL); also elsewhere on the board
P_K3: U1.F21 (PD9/RGMII_TXD1/MII_TXD1/RMII_TXD1); also elsewhere on the board
P_K4: U1.K18 (PD15/RGMII_CLKIN/MII_COL/RMII_NULL); also elsewhere on the board
P_L1: U1.E20 (PD8/RGMII_TXD2/MII_TXD2/RMII_NULL); also elsewhere on the board
P_L2: U1.B21 (PD6/RGMII_NULL/MII_RXERR/RMII_RXER); also elsewhere on the board
P_R1: U1.H18 (PD3/RGMII_RXD0/MII_RXD0/RMII_RXD0); also elsewhere on the board
P_R2: U1.E18 (PD7/RGMII_TXD3/MII_TXD3/RMII_NULL); also elsewhere on the board
P_RST: FPC54P.8 (/RESET), U$23.57 (P37/PWM2)
P_SCL: FPC54P.10 (SCL), U$23.58 (P07/RXD)
P_SDA: FPC54P.11 (SDI), U$23.59 (P06/TXD)
P_SELECT: U1.A20 (PD4/RGMII_RXCK/MII_RXCK/RMII_NULL); also elsewhere on the board
P_START: U1.H17 (PD1/RGMII_RXD2/MII_RXD2/RMII_NULL/DI_RX); also elsewhere on the board
R0: FPC54P.28 (R0), U$23.43 (B0/G3)
R1: FPC54P.29 (R1), U$23.44 (B1/G2)
R2: FPC54P.30 (R2), U$23.45 (B2/G1)
R3: FPC54P.31 (R3), U$23.46 (B3/G0)
R4: FPC54P.32 (R4), U$23.47 (B4/R7)
R5: FPC54P.33 (R5), U$23.48 (B5/R6)
R6: FPC54P.34 (R6), U$23.49 (B6/R5)
R7: FPC54P.35 (R7), U$23.50 (B7/R4)
S0BA0: U1.W17 (SBA0), U2.M2 (BA0), U3.M2 (BA0)
S0BA1: U1.T18 (SBA1), U2.N8 (BA1), U3.N8 (BA1)
S0BA2: U1.V17 (SBA2), U2.M3 (BA2), U3.M3 (BA2)
S0CASN: U1.U15 (SCAS), U2.K3 (#CAS), U3.K3 (#CAS)
S0CKE0: U1.AA21 (SCKE0), U2.K9 (CKE), U3.K9 (CKE)
S0CKE1: U1.Y21 (SCKE1), U2.J9 (NC), U3.J9 (NC)
S0CLK: DR8.2, U1.AA19 (SCK), U2.J7 (CK), U3.J7 (CK)
S0CLKN: DR8.1, U1.AA20 (SCKB), U2.K7 (#CK), U3.K7 (#CK)
S0DDR3_RST: U1.U16 (SRST), U2.T2 (#RESET), U3.T2 (#RESET)
S0DQ0: U1.N20 (SDQ0), U2.F8 (DQL3)
S0DQ1: U1.P21 (SDQ1), U2.H8 (DQL5)
S0DQ2: U1.P20 (SDQ2), U2.F7 (DQL1)
S0DQ3: U1.U21 (SDQ3), U2.E3 (DQL0)
S0DQ4: U1.R19 (SDQ4), U2.H7 (DQL7)
S0DQ5: U1.T20 (SDQ5), U2.F2 (DQL2)
S0DQ6: U1.U19 (SDQ6), U2.H3 (DQL4)
S0DQ7: U1.U20 (SDQ7), U2.G2 (DQL6)
S0DQ8: U1.J19 (SDQ8), U2.D7 (DQU0)
S0DQ9: U1.H20 (SDQ9), U2.C8 (DQU2)
S0DQ10: U1.H21 (SDQ10), U2.B8 (DQU6)
S0DQ11: U1.J21 (SDQ11), U2.A7 (DQU4)
S0DQ12: U1.L20 (SDQ12), U2.C3 (DQU1)
S0DQ13: U1.L21 (SDQ13), U2.C2 (DQU3)
S0DQ14: U1.M21 (SDQ14), U2.A2 (DQU5)
S0DQ15: U1.M19 (SDQ15), U2.A3 (DQU7)
S0DQ16: U1.Y17 (SDQ16), U3.F8 (DQL3)
S0DQ17: U1.AA17 (SDQ17), U3.H8 (DQL5)
S0DQ18: U1.Y16 (SDQ18), U3.H7 (DQL7)
S0DQ19: U1.W15 (SDQ19), U3.F7 (DQL1)
S0DQ20: U1.Y14 (SDQ20), U3.E3 (DQL0)
S0DQ21: U1.AA14 (SDQ21), U3.G2 (DQL6)
S0DQ22: U1.Y13 (SDQ22), U3.H3 (DQL4)
S0DQ23: U1.Y12 (SDQ23), U3.F2 (DQL2)
S0DQ24: U1.W12 (SDQ24), U3.C8 (DQU2)
S0DQ25: U1.AA11 (SDQ25), U3.B8 (DQU6)
S0DQ26: U1.Y11 (SDQ26), U3.A7 (DQU4)
S0DQ27: U1.Y10 (SDQ27), U3.D7 (DQU0)
S0DQ28: U1.W9 (SDQ28), U3.C3 (DQU1)
S0DQ29: U1.AA8 (SDQ29), U3.C2 (DQU3)
S0DQ30: U1.Y8 (SDQ30), U3.A3 (DQU7)
S0DQ31: U1.Y7 (SDQ31), U3.A2 (DQU5)
S0ODT0: U1.W11 (SODT0), U2.K1 (ODT), U3.K1 (ODT)
S0ODT1: U1.V11 (SODT1), U2.J1 (NC), U3.J1 (NC)
S0RASN: U1.V13 (SRAS), U2.J3 (#RAS), U3.J3 (#RAS)
S0SA0: U1.T17 (SA0), U2.N3 (A0), U3.N3 (A0)
S0SA1: U1.U18 (SA1), U2.P7 (A1), U3.P7 (A1)
S0SA2: U1.V19 (SA2), U2.P3 (A2), U3.P3 (A2)
S0SA3: U1.V20 (SA3), U2.N2 (A3), U3.N2 (A3)
S0SA4: U1.V21 (SA4), U2.P8 (A4), U3.P8 (A4)
S0SA5: U1.Y19 (SA5), U2.P2 (A5), U3.P2 (A5)
S0SA6: U1.Y20 (SA6), U2.R8 (A6), U3.R8 (A6)
S0SA7: U1.V15 (SA7), U2.R2 (A7), U3.R2 (A7)
S0SA8: U1.W18 (SA8), U2.T8 (A8), U3.T8 (A8)
S0SA9: U1.Y18 (SA9), U2.R3 (A9), U3.R3 (A9)
S0SA10: U1.P19 (SA10), U2.L7 (A10/AP), U3.L7 (A10/AP)
S0SA11: U1.N19 (SA11), U2.R7 (A11), U3.R7 (A11)
S0SA12: U1.R18 (SA12), U2.N7 (A12/#BC), U3.N7 (A12/#BC)
S0SA13: U1.V12 (SA13), U2.T3 (A13), U3.T3 (A13)
S0SA14: U1.N17 (SA14), U2.T7 (NC/A14), U3.T7 (NC/A14)
S0SA15: U1.R17 (SA15), U2.M7 (NC), U3.M7 (NC)
S0SCS0: U1.W20 (SCS0), U2.L2 (#CS), U3.L2 (#CS)
S0SCS1: U1.W21 (SCS1), U2.L1 (NC), U3.L1 (NC)
S0SDQM0: U1.M20 (SDQM0), U2.E7 (DML)
S0SDQM1: U1.G20 (SDQM1), U2.D3 (DMU)
S0SDQM2: U1.AA18 (SDQM2), U3.E7 (DML)
S0SDQM3: U1.AA12 (SDQM3), U3.D3 (DMU)
S0SDQS0: U1.R20 (SDQS0), U2.F3 (DQSL)
S0SDQS0_N: U1.R21 (SDQS0B), U2.G3 (#DQSL)
S0SDQS1: U1.K20 (SDQS1), U2.C7 (DQSU)
S0SDQS1_N: U1.J20 (SDQS1B), U2.B7 (#DQSU)
S0SDQS2: U1.AA15 (SDQS2), U3.F3 (DQSL)
S0SDQS2_N: U1.Y15 (SDQS2B), U3.G3 (#DQSL)
S0SDQS3: U1.AA9 (SDQS3), U3.C7 (DQSU)
S0SDQS3_N: U1.Y9 (SDQS3B), U3.B7 (#DQSU)
S0VREF: DC1.2, DC19.2, DC20.2, DC21.2, DC22.2, R3.2, R9.1, U1.T16 (SVREF), U2.H1 (VREFDQ), U2.M8 (VREFCA), U3.H1 (VREFDQ), U3.M8 (VREFCA)
S0WEN: U1.W13 (SWE), U2.L3 (#WE), U3.L3 (#WE)
SCL: PSCL.1, U$23.61 (RXD_SCL)
SD0-CLK: R22.2, U1.D20 (PF2/SDC0_CLK/UART0_TX)
SD0-CMD: MICRO_SD.3 (CMD/DI), R20.1, U1.F18 (PF3/SDC0_CMD/JTAG_DO0)
SD0-D0: MICRO_SD.7 (DAT0/DO), U1.A19 (PF1/SDC0_D0/JTAG_DI0)
SD0-D1: MICRO_SD.8 (DAT1/RES), U1.D19 (PF0/SDC0_D1/JTAG_MS0)
SD0-D2: MICRO_SD.1 (DAT2/RES), U1.C20 (PF5/SDC0_D2/JTAG_CK0)
SD0-D3: MICRO_SD.2 (CD/DAT3/CS), U1.E21 (PF4/SDC0_D3/UART0_RX)
SD0-DET#: MICRO_SD.9 (CP_E), R16.1, U1.G18 (PF6/SDC0_DET)
SDA: PSDA.1, U$23.60 (TXD_SDA)
SD_VCC: C67.2, L1.2, MICRO_SD.4 (VDD)
SPI_CLK: U$18.6 (SCK), U$23.20 (SPI_CLK)
SPI_CS: U$18.1 (CE#), U$23.17 (SPI_CS)
SPI_SI: U$18.2 (SO), U$23.18 (SPI_SI)
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
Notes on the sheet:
POWER SUPPLY CIRCUIT
2. Use 2(DDR3 512Mx16 Memory chips)x8Gb = 2GBytes, i.e. 2xH5TC8G63AMR-PBA(or K4B8G1646Q-MYK0)
MicroSD
The power options are:
3. 5V by microUSB if no battery
1. 3.7V Battery
=======================
Debug UART
HDMI
Ethernet
2. 3.5-5V on VBat if not battery
DDR3
1. Use 2(DDR3 256Mx16 Memory chips)x4Gb = 1GByte, i.e. 2xH5TQ4G63MFR-PBC(or K4B4G1646D-BCK0) -> Default
Options:
=======
PWR-STB
PWR-DRAM
PWRON/WORK
STANDBY
PWROFF
MODE
STATE
RetroStone Pi
???
wiring OK
wiring OK revoir R50-R83
wiring OK R20 10k ici 47k opi. OK
On/Off Switch GND=ON
Charge Rate = 1000V/PROG1
1.0K = 1000mA
2.0K = 500mA
Sur A13 SY8008C Sur opi0 SY8008B
0.8A
Or 100k/100k
USB
RDSon 2.5V = 70mOhm
ToDo: Ferrite (select w/high Z at high F, low Z at low F). Try to block everything >1MHz or so.
C3: Use 1uF to filter high frequency noise, or 10uF if lower frequency noise is present
NOTE: For the best power on/off pop performance, the amplifier should be set in the shutdown mode prior to power on/off operation (set SD low to power down the amp).
Opt out

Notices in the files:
buildroot-external/board/retrostone1/dts/sun8i-h3-retrostone1.dts:
SPDX-License-Identifier: (GPL-2.0+ OR MIT)
parts and their libraries:
microbuilder: This work is placed in the public domain, and may be freely used for commercial and non-commercial work with the following conditions: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
